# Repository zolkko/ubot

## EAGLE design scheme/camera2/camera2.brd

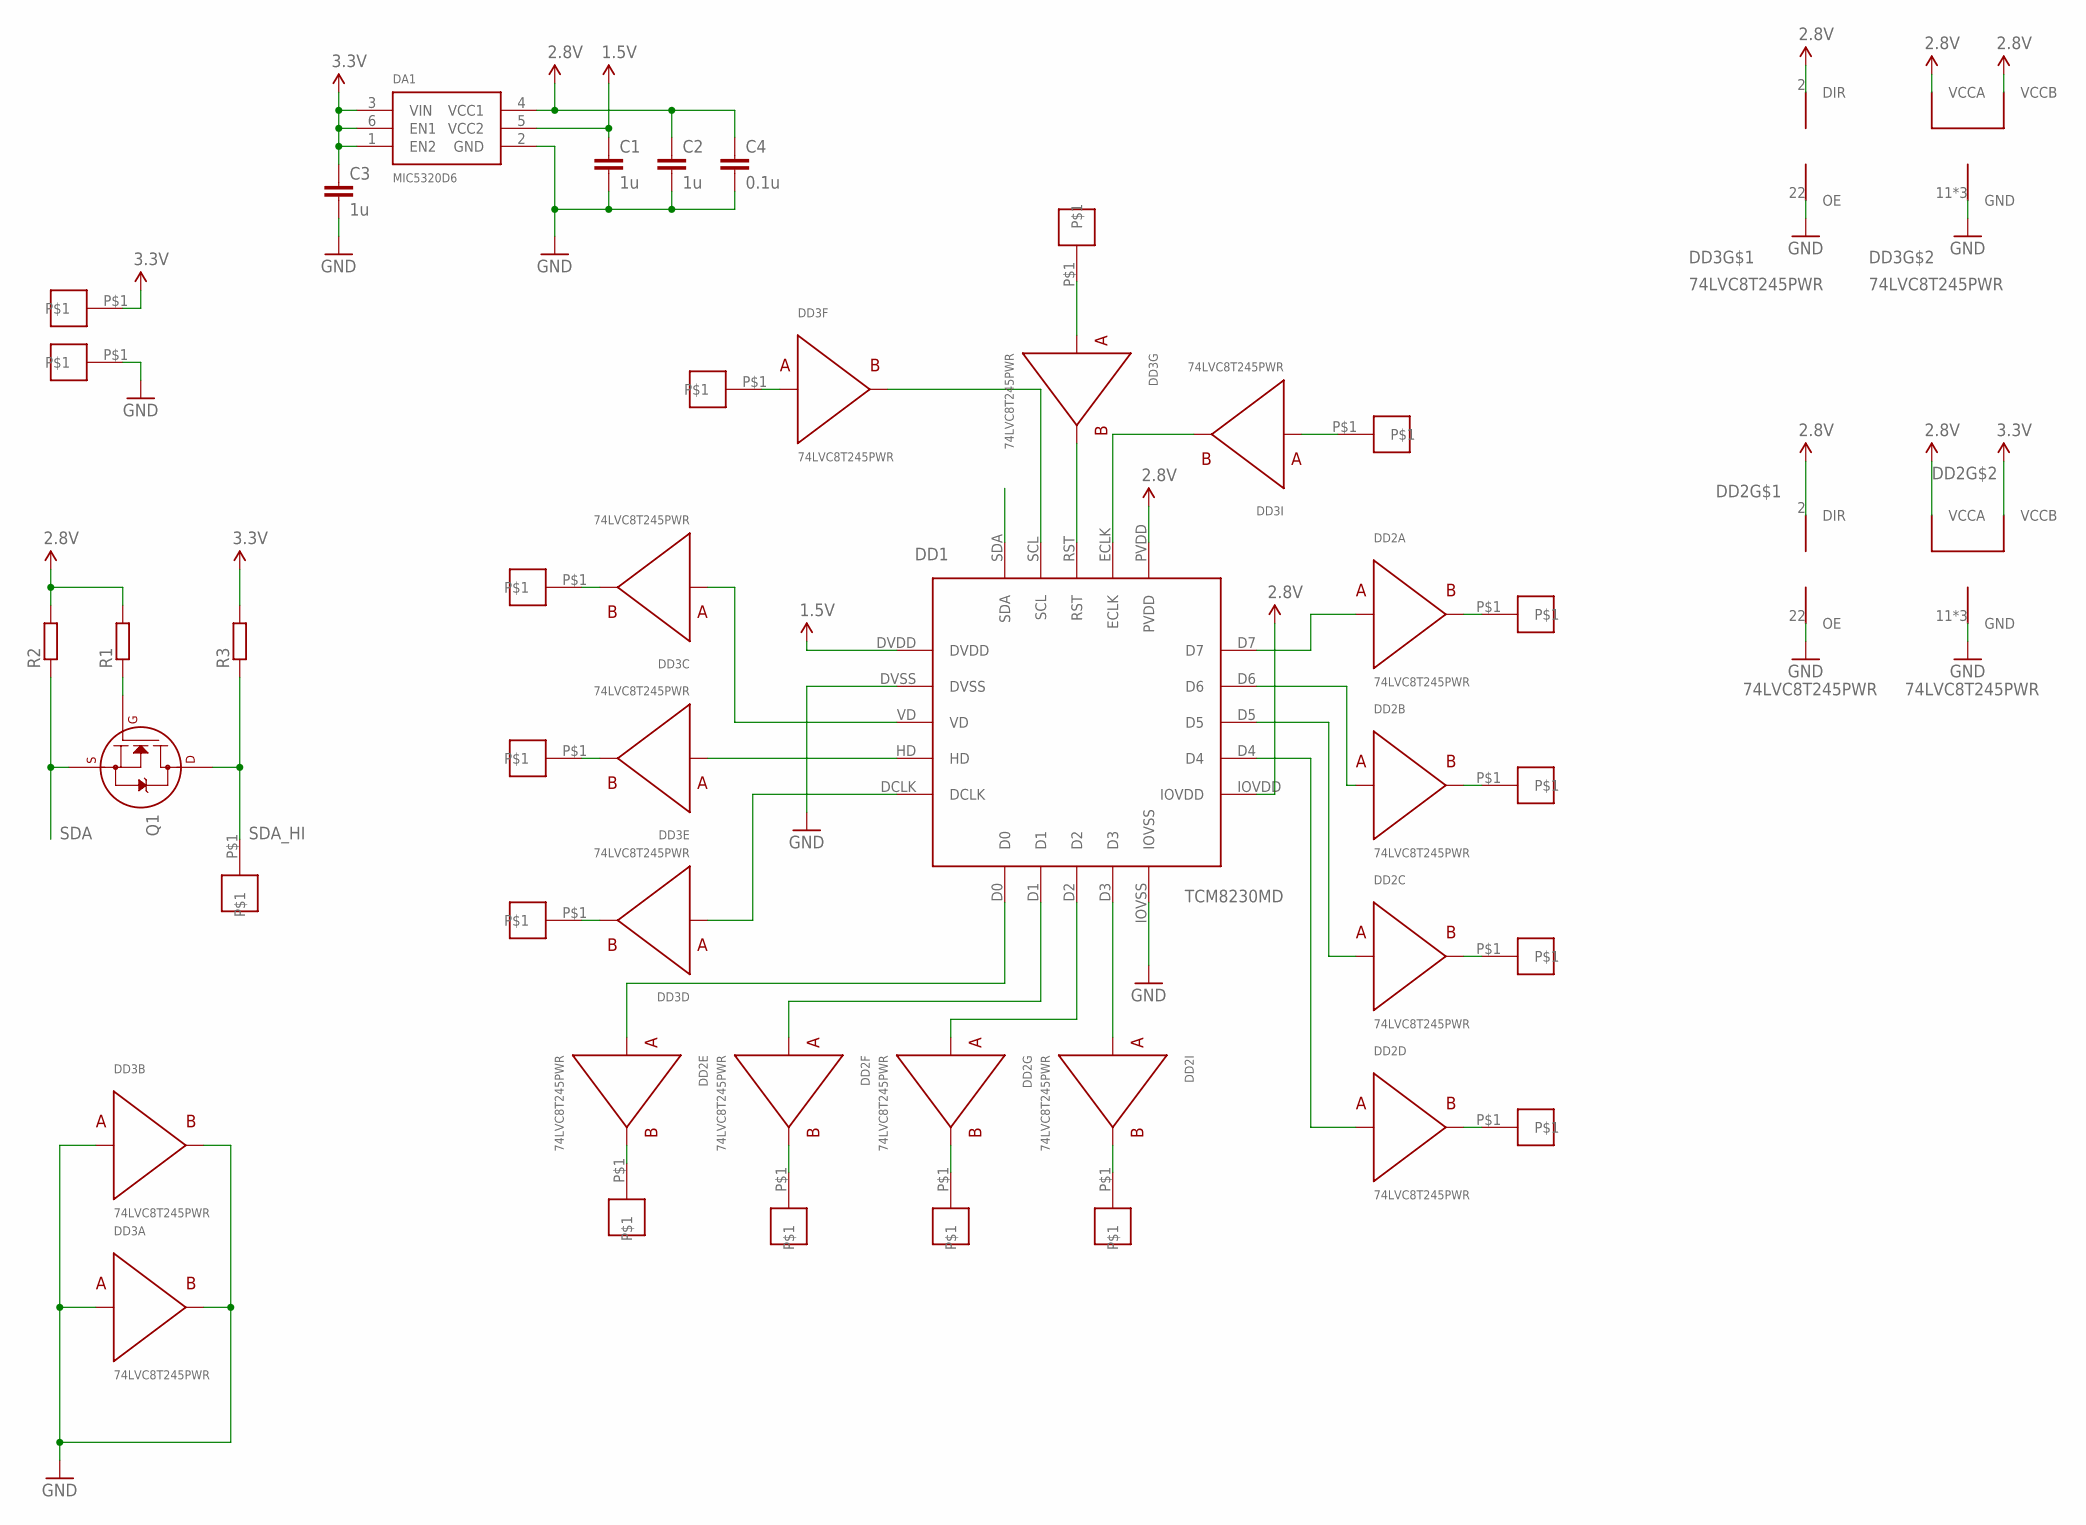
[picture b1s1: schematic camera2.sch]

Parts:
C1, C2, C3: 1u; C0603
C4: 0.1u; C0603
DA1: MIC5320D6; SOT23-6
DD1: TCM8230MD
DD2, DD3: 74LVC8T245PWR; TSSOP24
GND: HOLE
Q1: 2N7000_SOT23; SOT-23
R1, R2, R3: R-EU_R0603; R0603
SDAC: HOLE
SDLC: HOLE
U$27, U$30, U$31, U$32, U$33, U$34, U$35, U$36, U$37, U$38, U$39, U$40, U$41: HOLE
VDD: HOLE

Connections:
1.5V: C1.1, DA1.5 (VCC2), DD1.DVDD
2.8V: C2.1, C4.1, DA1.4 (VCC1), DD1.IOVDD, DD1.PVDD, DD2.1 (VCCA), DD2.2 (DIR), DD3.1 (VCCA), DD3.2 (DIR), DD3.23 (VCCB), DD3.24 (VCCB), R1.2, R2.2
3.3V: C3.1, DA1.1 (EN2), DA1.3 (VIN), DA1.6 (EN1), DD2.23 (VCCB), DD2.24 (VCCB), R3.2, VDD.P$1
D0_O: DD2.17 (B1), U$32.P$1
D1_O: DD2.16 (B1), U$31.P$1
D2_O: DD2.15 (B1), U$30.P$1
D3_O: DD2.14 (B1), U$27.P$1
D4_O: DD2.18 (B1), U$36.P$1
D5_O: DD2.19 (B1), U$35.P$1
D6_O: DD2.20 (B1), U$34.P$1
D7_O: DD2.21 (B1), U$33.P$1
DCLK_O: DD3.18 (B1), U$39.P$1
ECLK: DD1.ECLK, DD3.14 (B1)
ECLK_O: DD3.10 (A1), U$41.P$1
GND: C1.2, C2.2, C3.2, C4.2, DA1.2 (GND), DD1.DVSS, DD1.IOVSS, DD2.11 (GND), DD2.12 (GND), DD2.13 (GND), DD2.22 (OE), DD3.3 (A1), DD3.4 (A1), DD3.11 (GND), DD3.12 (GND), DD3.13 (GND), DD3.20 (B1), DD3.21 (B1), DD3.22 (OE), GND.P$1
HD_O: DD3.17 (B1), U$38.P$1
unnamed: DD1.D3, DD2.10 (A1)
unnamed: DD1.D7, DD2.3 (A1)
unnamed: DD1.D6, DD2.4 (A1)
unnamed: DD1.D5, DD2.5 (A1)
unnamed: DD1.D4, DD2.6 (A1)
unnamed: DD1.D0, DD2.7 (A1)
unnamed: DD1.D2, DD2.9 (A1)
unnamed: DD1.D1, DD2.8 (A1)
unnamed: DD1.VD, DD3.5 (A1)
unnamed: DD1.HD, DD3.7 (A1)
unnamed: Q1.1 (G), R1.1
unnamed: DD1.DCLK, DD3.6 (A1)
unnamed: DD1.RST, DD3.15 (B1)
RST_O: DD3.9 (A1), U$40.P$1
SDA: DD1.SDA, Q1.2 (S), R2.1
SDA_HI: Q1.3 (D), R3.1, SDAC.P$1
SDL: DD1.SCL, DD3.16 (B1)
SDL_IN: DD3.8 (A1), SDLC.P$1
VD_O: DD3.19 (B1), U$37.P$1

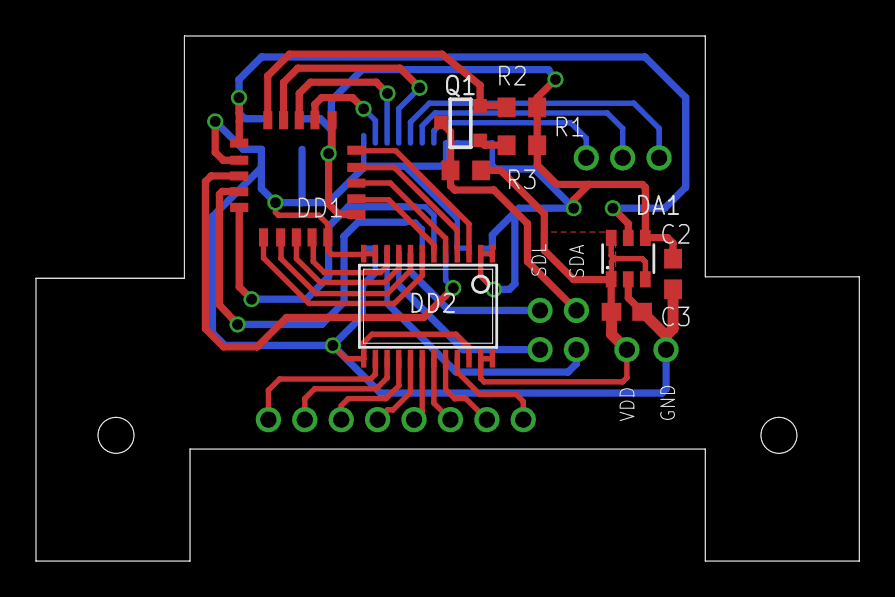
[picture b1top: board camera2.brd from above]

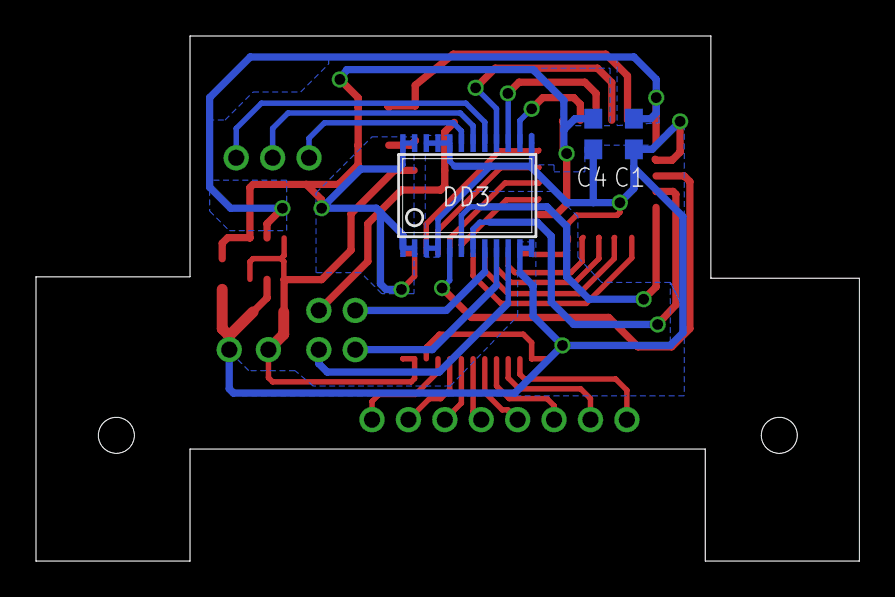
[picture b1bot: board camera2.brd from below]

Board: 2 copper layers, 45.7 x 29.2 mm, 29 parts (3 on the bottom side), 35 nets.

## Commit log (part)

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2013-02-26 roboserv test
2013-02-26 presentation
2013-02-26 echo rtc sample
2013-02-26 gitignore
2013-02-26 minor changes
2013-02-27 base udpserver has been added
2013-02-27 partial changes
2013-02-28 ignore changed
2013-02-28 ortpy initial
2013-03-04 signal handling has been added
2013-03-04 sdp line fix
2013-03-04 minor sdp fix
2013-03-26 set_remote_addr method has been added
2013-05-05 camera2 has been added
2013-05-20 presentation has been changed
